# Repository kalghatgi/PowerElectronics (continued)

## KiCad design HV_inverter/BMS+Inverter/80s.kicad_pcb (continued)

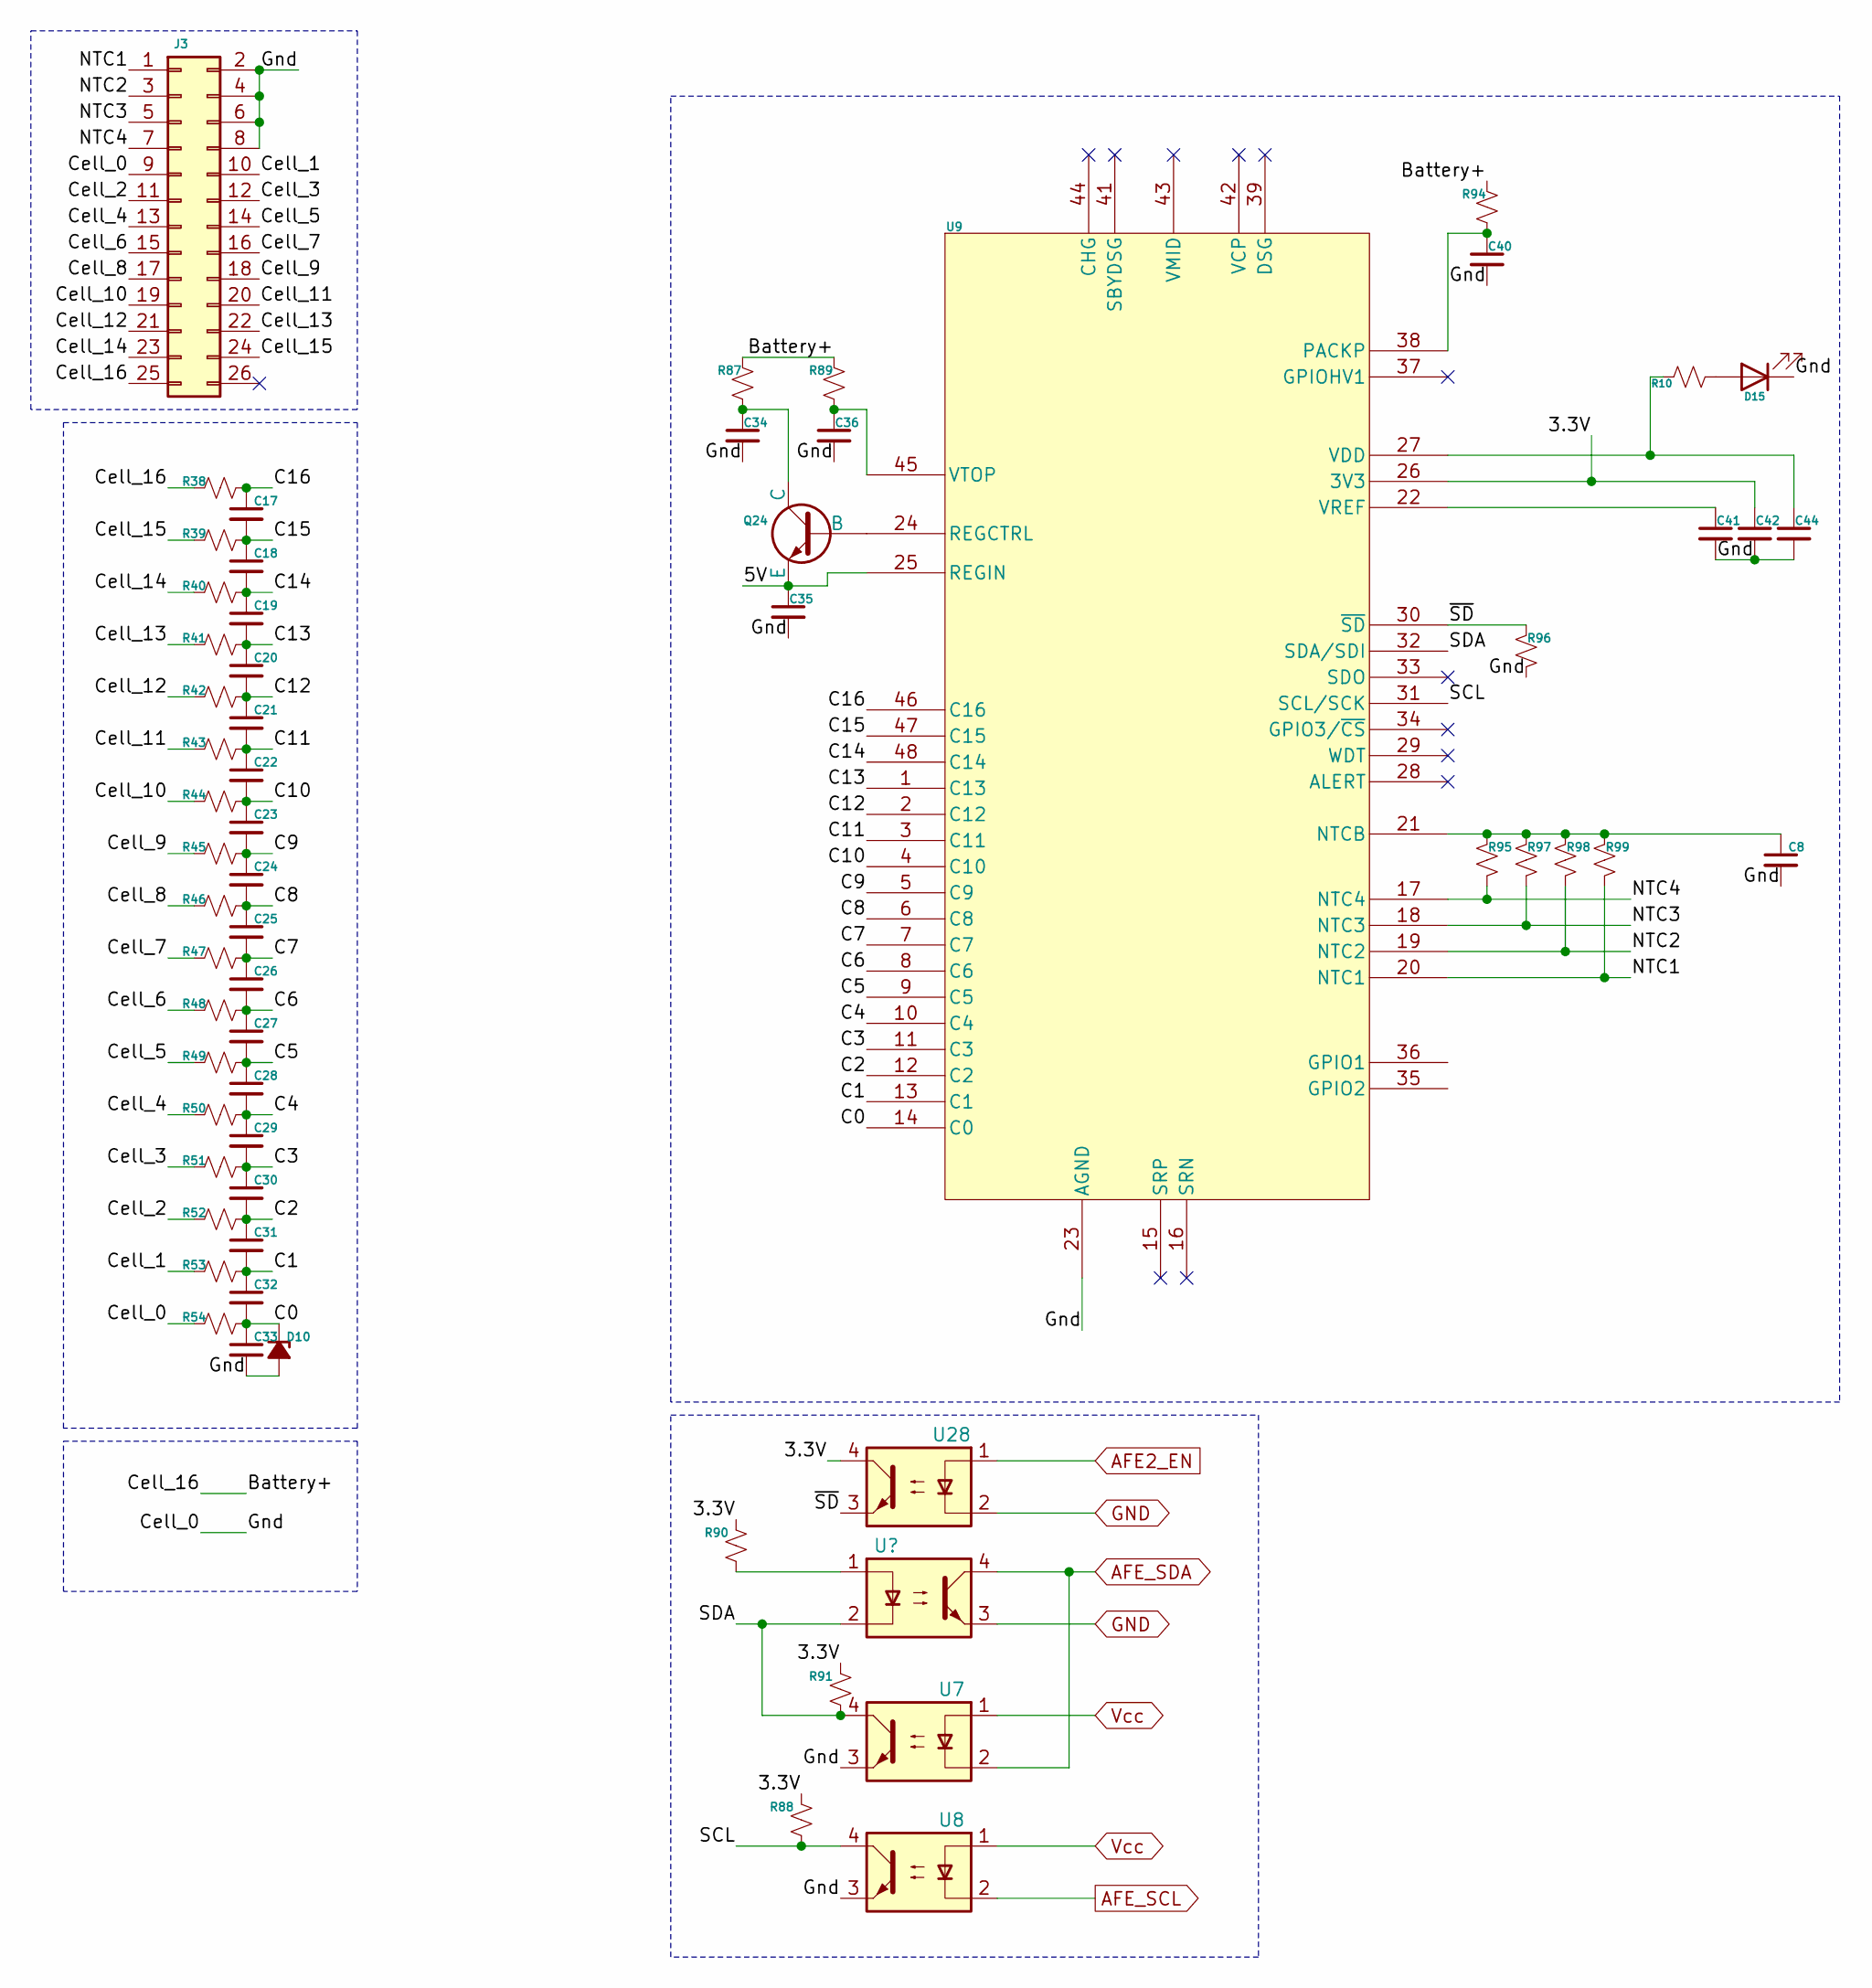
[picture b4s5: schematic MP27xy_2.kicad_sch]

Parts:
C8, C17, C18, C19, C20, C21, C22, C23, C24, C25, C26, C27, C28, C29, C30, C31, C32, C33: 10000pF, >=10V, 0402; C_0402_1005Metric; MPN grm155r61c103ka01d
C34: 1uF, >=100V, 0805; C_0805_2012Metric; MPN grm21bc72a105ke01l
C35: 3.3uF, >=10V, 0402; C_0402_1005Metric
C36: 0.47uF, >=100V, 0805; C_0805_2012Metric; MPN cc0805kkx7r0bb474
C40: 10nF, >=100V, 0805; C_0805_2012Metric; MPN c0805c103k1ractu
C41, C42, C44: 1uF, >=6.3V, 0402; C_0402_1005Metric; MPN cl05a105kq5nnnc
D10: VR=3.3V; D_SOD-323; MPN bzx384c3v3-e3-08
D15: LED-Red 0402; LED_0402_1005Metric
J3: 2x13 pin; IDC-Header_2x13_P2.54mm_Horizontal
Q24: NPN, 80V, 0.5A; SOT-23; MPN mmbt5550lt1g
R10, R95, R96, R97, R98, R99: 10K, >=62.5mW, 0402; R_0402_1005Metric; MPN mcwr04x1002ftl
R38, R39, R40, R41, R42, R43, R44, R45, R46, R47, R48, R49, R50, R51, R52, R53, R54: 1K, >=62.5mW, 0402; R_0402_1005Metric; MPN mcwr04x1001ftl
R87: 500E, >=100mW, 0603; R_0603_1608Metric; MPN rt0603brc07500rl
R88, R90, R91: 1.5K, >=62.5mW, 0402; R_0402_1005Metric; MPN mcwr04x1501ftl
R89: 20E, >=100mW, 0603; R_0603_1608Metric; MPN mcwr06x20r0ftl
R94: 100E, >=100mW, 0603; R_0603_1608Metric; MPN mcwr06x101-jtl
U6, U7, U8, U28: PC817; DIP-4_W7.62mm
U9: MP2787; TQFP-48_7x7mm_P0.5mm; MPN MP2787DFP-0001-T

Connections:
/CMU2/3.3V: C42.1, R88.2, R90.2, R91.2, U9.26 (3V3), U28.4
/CMU2/5V: C35.1, Q24.2 (E), U9.25 (REGIN)
/CMU2/Battery+: J3.25, R38.2, R87.2, R89.2, R94.2
/CMU2/C0: C32.2, C33.1, D10.1 (K), R54.1, U9.14 (C0)
/CMU2/C1: C31.2, C32.1, R53.1, U9.13 (C1)
/CMU2/C2: C30.2, C31.1, R52.1, U9.12 (C2)
/CMU2/C3: C29.2, C30.1, R51.1, U9.11 (C3)
/CMU2/C4: C28.2, C29.1, R50.1, U9.10 (C4)
/CMU2/C5: C27.2, C28.1, R49.1, U9.9 (C5)
/CMU2/C6: C26.2, C27.1, R48.1, U9.8 (C6)
/CMU2/C7: C25.2, C26.1, R47.1, U9.7 (C7)
/CMU2/C8: C24.2, C25.1, R46.1, U9.6 (C8)
/CMU2/C9: C23.2, C24.1, R45.1, U9.5 (C9)
/CMU2/C10: C22.2, C23.1, R44.1, U9.4 (C10)
/CMU2/C11: C21.2, C22.1, R43.1, U9.3 (C11)
/CMU2/C12: C20.2, C21.1, R42.1, U9.2 (C12)
/CMU2/C13: C19.2, C20.1, R41.1, U9.1 (C13)
/CMU2/C14: C18.2, C19.1, R40.1, U9.48 (C14)
/CMU2/C15: C17.2, C18.1, R39.1, U9.47 (C15)
/CMU2/C16: C17.1, R38.1, U9.46 (C16)
/CMU2/Cell_0: C8.2, C33.2, C34.2, C35.2, C36.2, C40.2, C41.2, C42.2, C44.2, D10.2 (A), D15.1 (K), J3.2, J3.4, J3.6, J3.8, J3.9, R54.2, R96.2, U7.3, U8.3, U9.23 (AGND)
/CMU2/Cell_1: J3.10, R53.2
/CMU2/Cell_2: J3.11, R52.2
/CMU2/Cell_3: J3.12, R51.2
/CMU2/Cell_4: J3.13, R50.2
/CMU2/Cell_5: J3.14, R49.2
/CMU2/Cell_6: J3.15, R48.2
/CMU2/Cell_7: J3.16, R47.2
/CMU2/Cell_8: J3.17, R46.2
/CMU2/Cell_9: J3.18, R45.2
/CMU2/Cell_10: J3.19, R44.2
/CMU2/Cell_11: J3.20, R43.2
/CMU2/Cell_12: J3.21, R42.2
/CMU2/Cell_13: J3.22, R41.2
/CMU2/Cell_14: J3.23, R40.2
/CMU2/Cell_15: J3.24, R39.2
/CMU2/NTC1: J3.1, R99.2, U9.20 (NTC1)
/CMU2/NTC2: J3.3, R98.2, U9.19 (NTC2)
/CMU2/NTC3: J3.5, R97.2, U9.18 (NTC3)
/CMU2/NTC4: J3.7, R95.2, U9.17 (NTC4)
/CMU2/SCL: R88.1, U8.4, U9.31 (SCL/SCK)
/CMU2/SDA: R91.1, U6.2, U7.4, U9.32 (SDA/SDI)
/CMU2/~SD: R96.1, U9.30 (~SD), U28.3
AFE2_EN: U28.1; also elsewhere on the board
AFE_SCL: U8.2; also elsewhere on the board
AFE_SDA: U6.4, U7.2; also elsewhere on the board
GND: U6.3, U28.2; also elsewhere on the board
unnamed: D15.2 (A), R10.1
unnamed: Q24.1 (B), U9.24 (REGCTRL)
unnamed: C34.1, Q24.3 (C), R87.1
unnamed: R90.1, U6.1
unnamed: C8.1, R95.1, R97.1, R98.1, R99.1, U9.21 (NTCB)
unnamed: C40.1, R94.1, U9.38 (PACKP)
unnamed: C44.1, R10.2, U9.27 (VDD)
unnamed: C41.1, U9.22 (VREF)
unnamed: C36.1, R89.1, U9.45 (VTOP)
Vcc: U7.1, U8.1; also elsewhere on the board

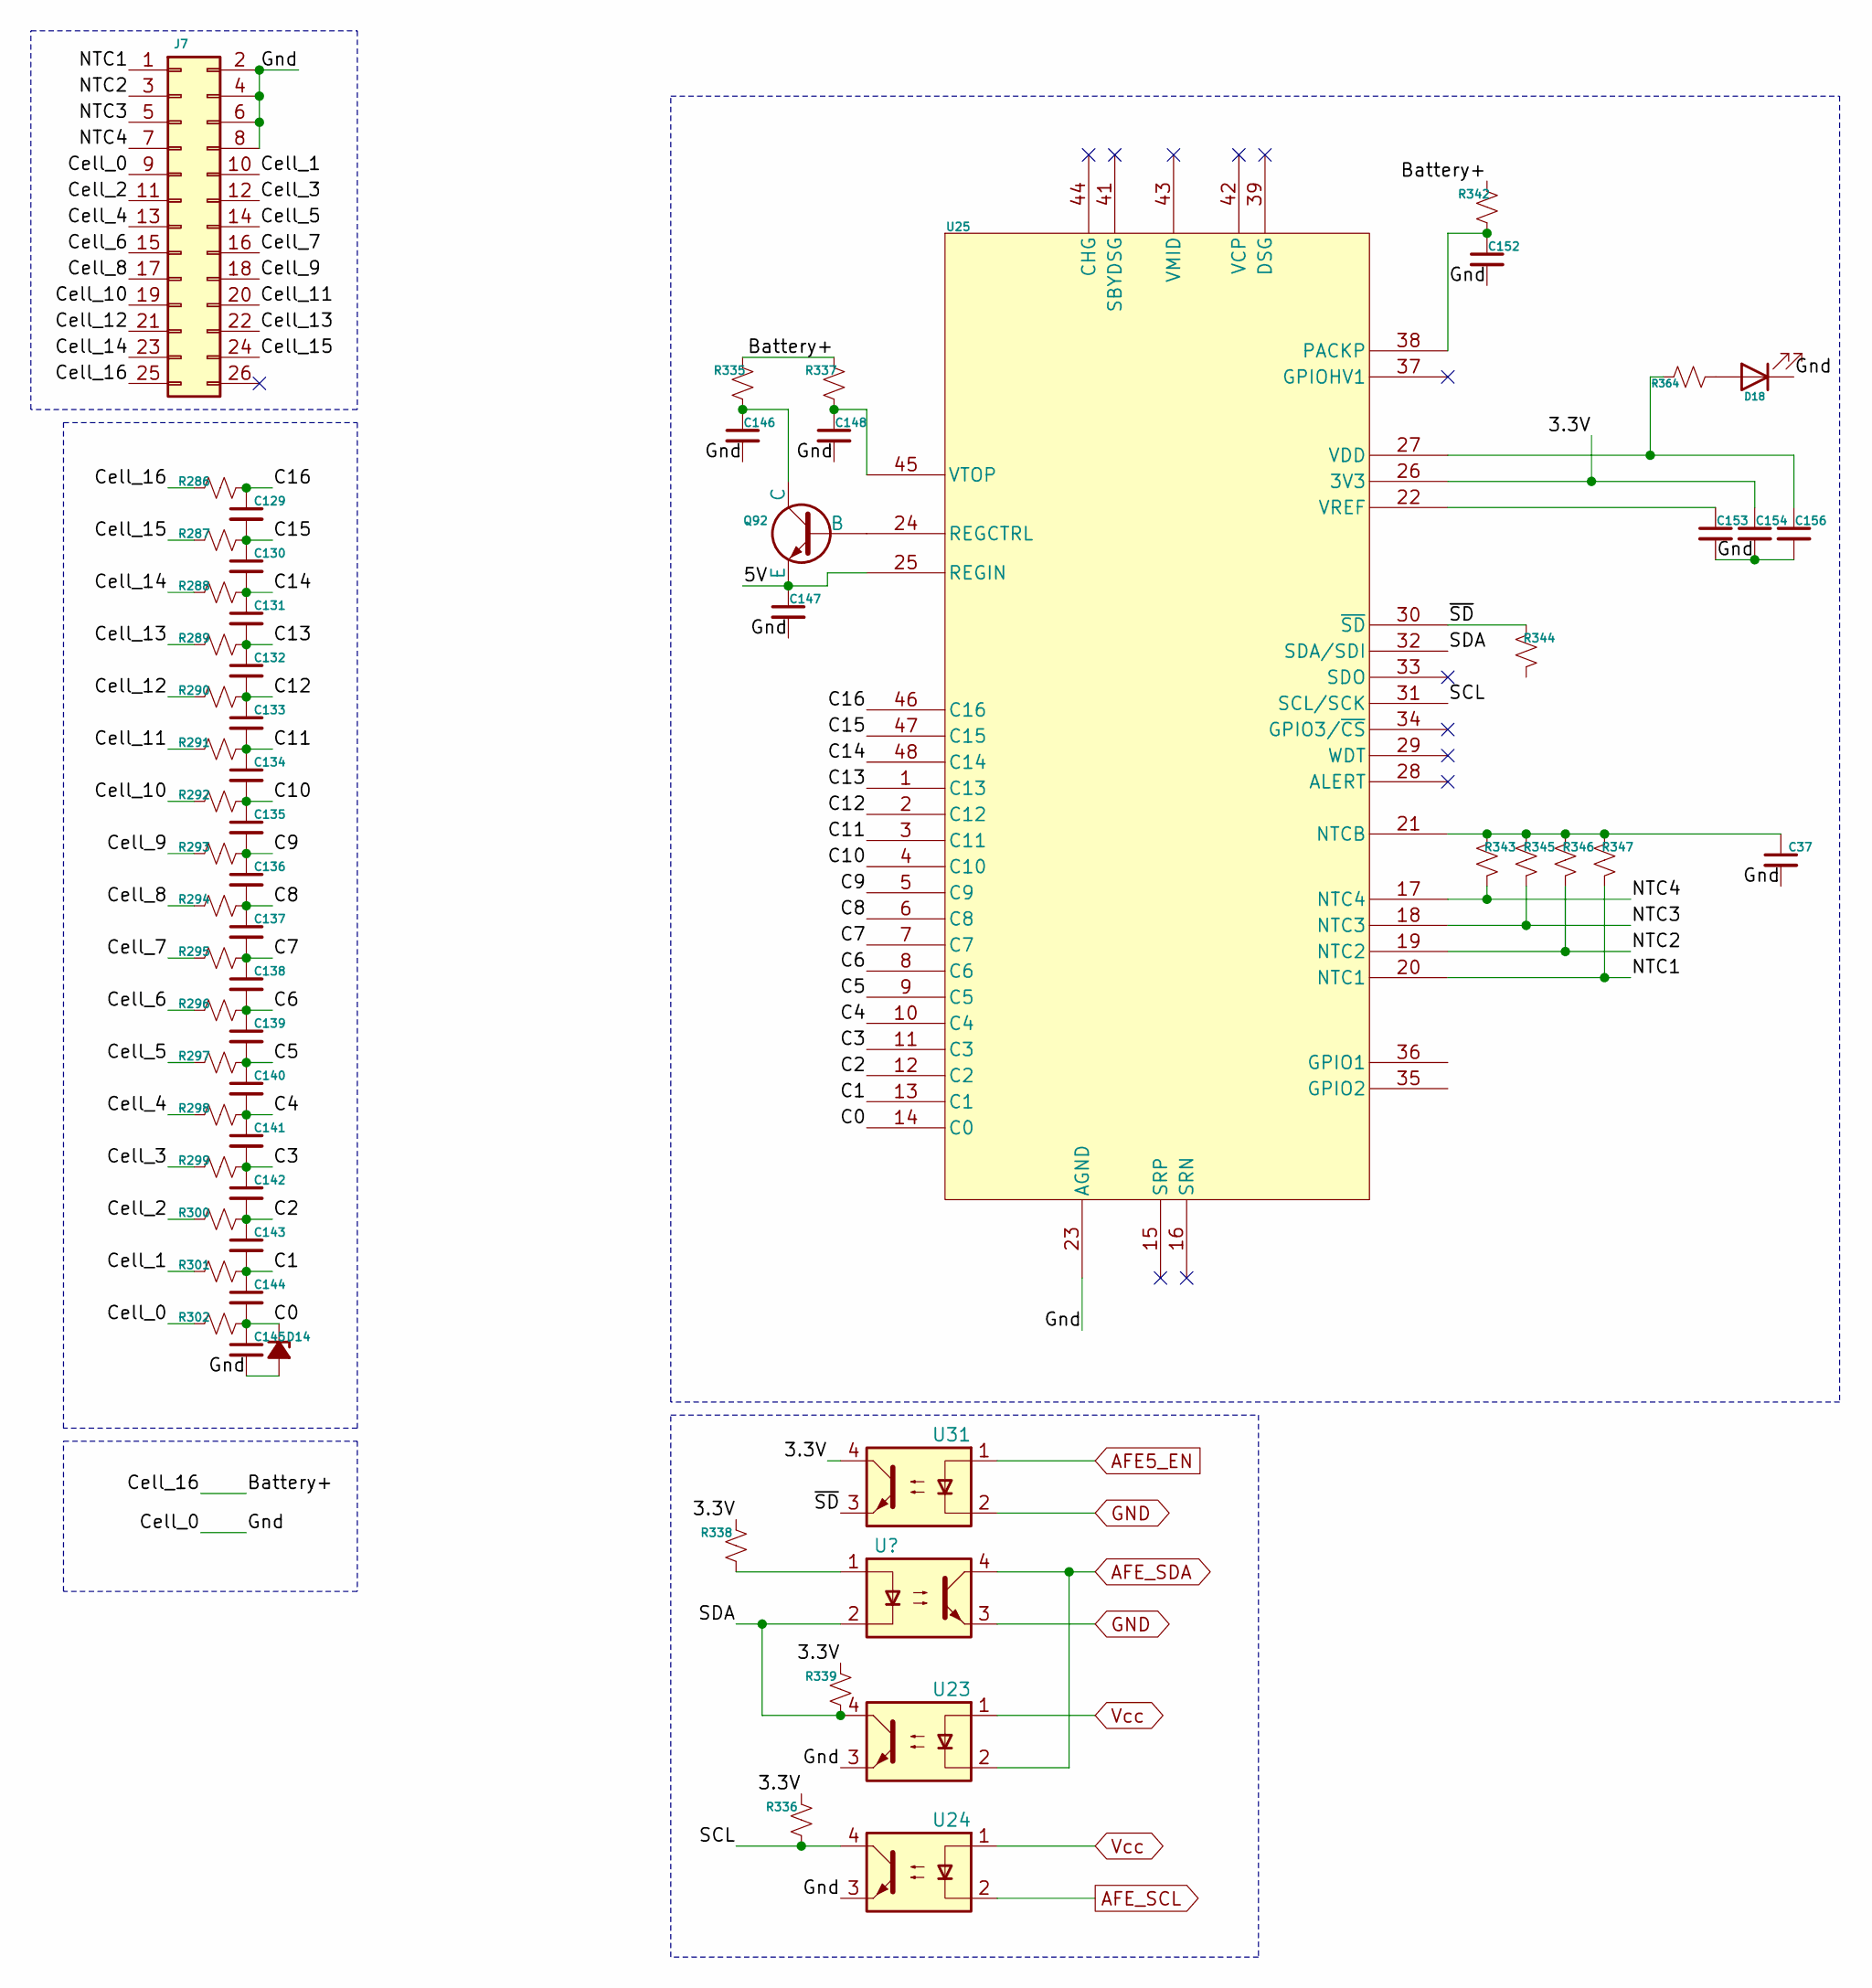
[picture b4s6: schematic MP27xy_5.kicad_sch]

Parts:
C37, C129, C130, C131, C132, C133, C134, C135, C136, C137, C138, C139, C140, C141, C142, C143, C144, C145: 10000pF, >=10V, 0402; C_0402_1005Metric; MPN grm155r61c103ka01d
C146: 1uF, >=100V, 0805; C_0805_2012Metric; MPN grm21bc72a105ke01l
C147: 3.3uF, >=10V, 0402; C_0402_1005Metric
C148: 0.47uF, >=100V, 0805; C_0805_2012Metric; MPN cc0805kkx7r0bb474
C152: 10nF, >=100V, 0805; C_0805_2012Metric; MPN c0805c103k1ractu
C153, C154, C156: 1uF, >=6.3V, 0402; C_0402_1005Metric; MPN cl05a105kq5nnnc
D14: VR=3.3V; D_SOD-323; MPN bzx384c3v3-e3-08
D18: LED-Red 0402; LED_0402_1005Metric
J7: 2x13 pin; IDC-Header_2x13_P2.54mm_Horizontal
Q92: NPN, 80V, 0.5A; SOT-23; MPN mmbt5550lt1g
R286, R287, R288, R289, R290, R291, R292, R293, R294, R295, R296, R297, R298, R299, R300, R301, R302: 1K, >=62.5mW, 0402; R_0402_1005Metric; MPN mcwr04x1001ftl
R335: 500E, >=100mW, 0603; R_0603_1608Metric; MPN rt0603brc07500rl
R336, R338, R339: 1.5K, >=62.5mW, 0402; R_0402_1005Metric; MPN mcwr04x1501ftl
R337: 20E, >=100mW, 0603; R_0603_1608Metric; MPN mcwr06x20r0ftl
R342: 100E, >=100mW, 0603; R_0603_1608Metric; MPN mcwr06x101-jtl
R343, R344, R345, R346, R347, R364: 10K, >=62.5mW, 0402; R_0402_1005Metric; MPN mcwr04x1002ftl
U22, U23, U24, U31: PC817; DIP-4_W7.62mm
U25: MP2787; TQFP-48_7x7mm_P0.5mm; MPN MP2787DFP-0001-T

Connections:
/CMU5/3.3V: C154.1, R336.2, R338.2, R339.2, U25.26 (3V3), U31.4
/CMU5/5V: C147.1, Q92.2 (E), U25.25 (REGIN)
/CMU5/Battery+: J7.25, R286.2, R335.2, R337.2, R342.2
/CMU5/C0: C144.2, C145.1, D14.1 (K), R302.1, U25.14 (C0)
/CMU5/C1: C143.2, C144.1, R301.1, U25.13 (C1)
/CMU5/C2: C142.2, C143.1, R300.1, U25.12 (C2)
/CMU5/C3: C141.2, C142.1, R299.1, U25.11 (C3)
/CMU5/C4: C140.2, C141.1, R298.1, U25.10 (C4)
/CMU5/C5: C139.2, C140.1, R297.1, U25.9 (C5)
/CMU5/C6: C138.2, C139.1, R296.1, U25.8 (C6)
/CMU5/C7: C137.2, C138.1, R295.1, U25.7 (C7)
/CMU5/C8: C136.2, C137.1, R294.1, U25.6 (C8)
/CMU5/C9: C135.2, C136.1, R293.1, U25.5 (C9)
/CMU5/C10: C134.2, C135.1, R292.1, U25.4 (C10)
/CMU5/C11: C133.2, C134.1, R291.1, U25.3 (C11)
/CMU5/C12: C132.2, C133.1, R290.1, U25.2 (C12)
/CMU5/C13: C131.2, C132.1, R289.1, U25.1 (C13)
/CMU5/C14: C130.2, C131.1, R288.1, U25.48 (C14)
/CMU5/C15: C129.2, C130.1, R287.1, U25.47 (C15)
/CMU5/C16: C129.1, R286.1, U25.46 (C16)
/CMU5/Cell_0: C37.2, C145.2, C146.2, C147.2, C148.2, C152.2, C153.2, C154.2, C156.2, D14.2 (A), D18.1 (K), J7.2, J7.4, J7.6, J7.8, J7.9, R302.2, U23.3, U24.3, U25.23 (AGND)
/CMU5/Cell_1: J7.10, R301.2
/CMU5/Cell_2: J7.11, R300.2
/CMU5/Cell_3: J7.12, R299.2
/CMU5/Cell_4: J7.13, R298.2
/CMU5/Cell_5: J7.14, R297.2
/CMU5/Cell_6: J7.15, R296.2
/CMU5/Cell_7: J7.16, R295.2
/CMU5/Cell_8: J7.17, R294.2
/CMU5/Cell_9: J7.18, R293.2
/CMU5/Cell_10: J7.19, R292.2
/CMU5/Cell_11: J7.20, R291.2
/CMU5/Cell_12: J7.21, R290.2
/CMU5/Cell_13: J7.22, R289.2
/CMU5/Cell_14: J7.23, R288.2
/CMU5/Cell_15: J7.24, R287.2
/CMU5/NTC1: J7.1, R347.2, U25.20 (NTC1)
/CMU5/NTC2: J7.3, R346.2, U25.19 (NTC2)
/CMU5/NTC3: J7.5, R345.2, U25.18 (NTC3)
/CMU5/NTC4: J7.7, R343.2, U25.17 (NTC4)
/CMU5/SCL: R336.1, U24.4, U25.31 (SCL/SCK)
/CMU5/SDA: R339.1, U22.2, U23.4, U25.32 (SDA/SDI)
/CMU5/~SD: R344.1, U25.30 (~SD), U31.3
AFE5_EN: U31.1; also elsewhere on the board
AFE_SCL: U24.2; also elsewhere on the board
AFE_SDA: U22.4, U23.2; also elsewhere on the board
GND: U22.3, U31.2; also elsewhere on the board
unnamed: D18.2 (A), R364.1
unnamed: Q92.1 (B), U25.24 (REGCTRL)
unnamed: C146.1, Q92.3 (C), R335.1
unnamed: R338.1, U22.1
unnamed: C37.1, R343.1, R345.1, R346.1, R347.1, U25.21 (NTCB)
unnamed: C152.1, R342.1, U25.38 (PACKP)
unnamed: C156.1, R364.2, U25.27 (VDD)
unnamed: C153.1, U25.22 (VREF)
unnamed: C148.1, R337.1, U25.45 (VTOP)
Vcc: U23.1, U24.1; also elsewhere on the board

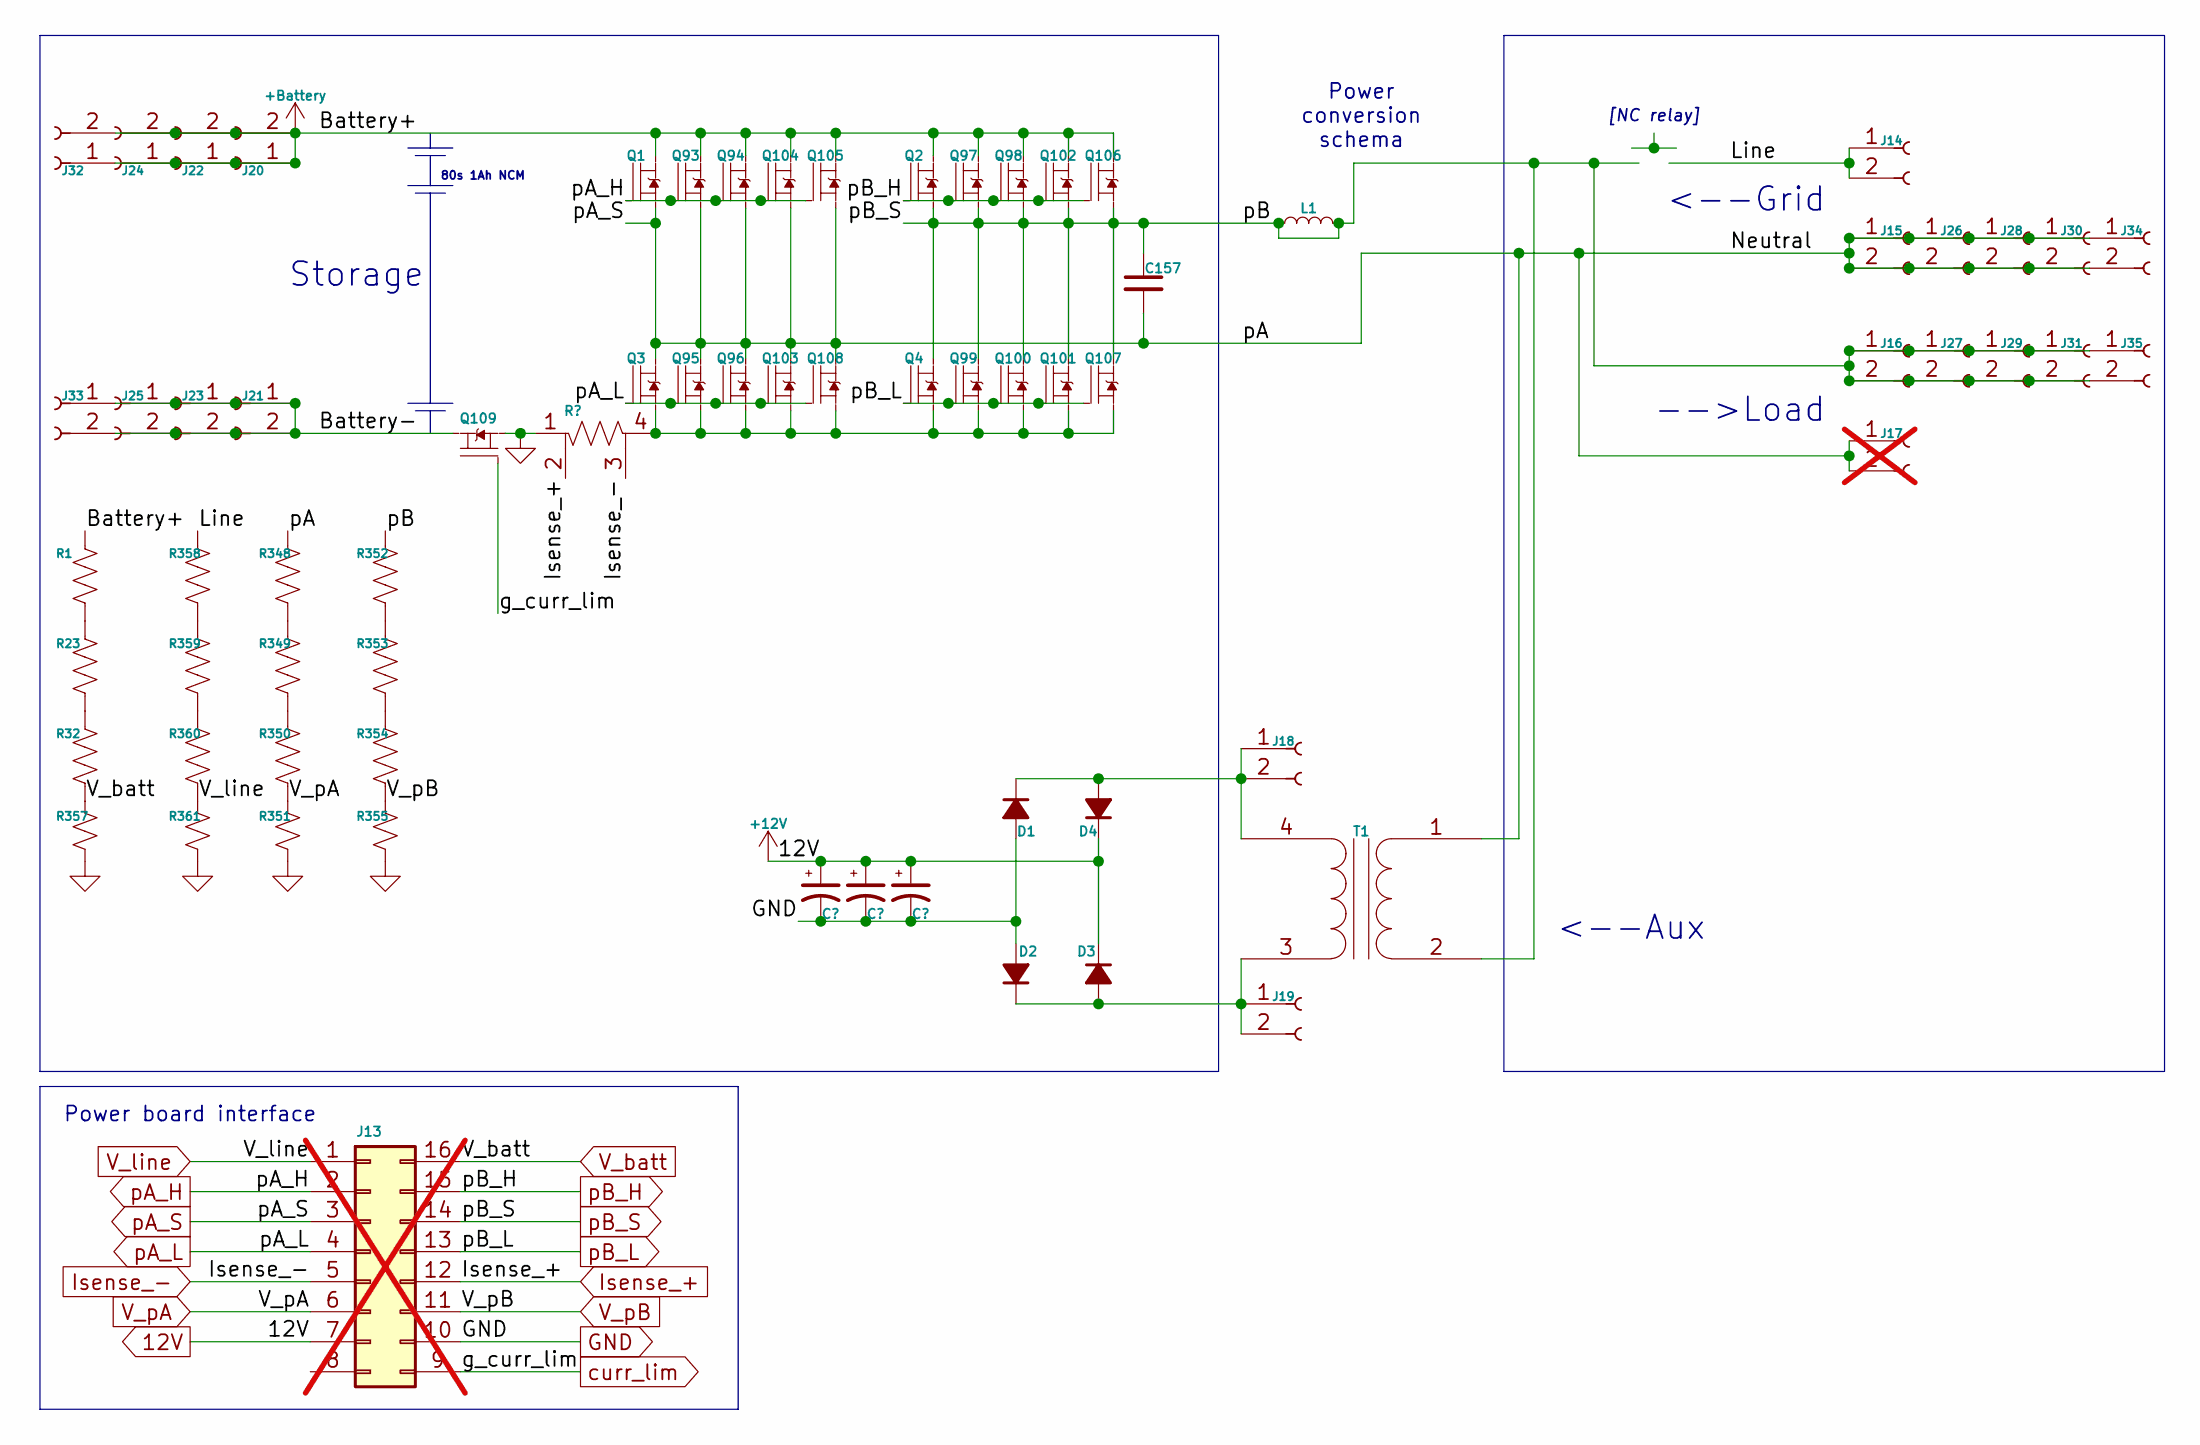
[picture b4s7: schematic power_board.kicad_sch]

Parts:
C157: 1uF, >500V; C_2220_5750Metric; MPN 2220CC105KAZ2A
C159, C160, C161: 100uF, >25V; C_Radial_D6.3mm_H5.0mm_P2.50mm
D1, D2, D3, D4: Vr>400V, If>2A; D_SOD-123F; MPN SL1A
J13: 2x7 pin, 2.54mm pitch; PinSocket_2x07_P2.54mm_Vertical; not fitted
J14, J15, J16, J18, J19, J20, J21, J22, J23, J24, J25, J26, J27, J28, J29, J30, J31, J32, J33, J34, J35: 2pin, >400V, >20A; TE_62409-1; MPN DJ6112
J17: 2pin, >400V, >20A; TE_62409-1; MPN DJ6112; not fitted
L1: L_Small
Q1, Q2, Q3, Q4, Q93, Q94, Q95, Q96, Q97, Q98, Q99, Q100, Q101, Q102, Q103, Q104, Q105, Q106, Q107, Q108: NMOS, Vds>=400V, Rds<=50mOhm; IPDQ60R037CM8XTMA1; MPN IPDQ60R037CM8XTMA1
Q109: NMOS, Vds>=80V, Rds<=2mOhm; Infineon_PG-TDSON-8_6.15x5.15mm; MPN IAUCN08S7N013ATMA1
R1, R23, R32, R348, R349, R350, R352, R353, R354, R358, R359, R360: 1MOhm, >200V, <1%, >62.5mW; R_1206_3216Metric
R351, R355, R357, R361: 10K, >62.5mW; R_0603_1608Metric
R356: 10mOhm, >=3W; R_shunt_2512_6332Metric; MPN CRA2512-FZ-R010ELF
T1: Vin=230V, Vout=12V, Iout=0.3A

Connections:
12V: C159.1, C160.1, C161.1, D3.1 (K), D4.1 (K), J13.7; also elsewhere on the board
+Battery: J20.1, J20.2, J22.1, J22.2, J24.1, J24.2, J32.1, J32.2, Q1.3 (D), Q2.3 (D), Q93.3 (D), Q94.3 (D), Q97.3 (D), Q98.3 (D), Q102.3 (D), Q104.3 (D), Q105.3 (D), Q106.3 (D), R1.1
/Power/Battery-: J21.1, J21.2, J23.1, J23.2, J25.1, J25.2, J33.1, J33.2, Q109.5 (D)
/Power/Line: J14.1, J14.2, R358.1
GND: C159.2, C160.2, C161.2, D1.2 (A), D2.2 (A), J13.10, Q109.1 (S), Q109.2 (S), Q109.3 (S), R351.2, R355.2, R356.1, R357.2, R361.2; also elsewhere on the board
Isense_+: J13.12, R356.2; also elsewhere on the board
Isense_-: J13.5, R356.3; also elsewhere on the board
unnamed: D1.1 (K), D4.2 (A), J18.1, J18.2, T1.4 (SB)
unnamed: D2.1 (K), D3.2 (A), J19.1, J19.2, T1.3 (SA)
unnamed: Q3.2 (S), Q4.2 (S), Q95.2 (S), Q96.2 (S), Q99.2 (S), Q100.2 (S), Q101.2 (S), Q103.2 (S), Q107.2 (S), Q108.2 (S), R356.4
unnamed: R1.2, R23.1
unnamed: R23.2, R32.1
unnamed: R348.2, R349.1
unnamed: R349.2, R350.1
unnamed: R352.2, R353.1
unnamed: R353.2, R354.1
unnamed: R358.2, R359.1
unnamed: R359.2, R360.1
V_batt: J13.16, R32.2, R357.1; also elsewhere on the board
V_line: J13.1, R360.2, R361.1; also elsewhere on the board
V_pA: J13.6, R350.2, R351.1; also elsewhere on the board
V_pB: J13.11, R354.2, R355.1; also elsewhere on the board
curr_lim: J13.9, Q109.4 (G); also elsewhere on the board
pA_H: J13.2, Q1.1 (G), Q93.1 (G), Q94.1 (G), Q104.1 (G), Q105.1 (G); also elsewhere on the board
pA_L: J13.4, Q3.1 (G), Q95.1 (G), Q96.1 (G), Q103.1 (G), Q108.1 (G); also elsewhere on the board
pA_S: C157.2, J13.3, J15.1, J15.2, J17.1, J17.2, J26.1, J26.2, J28.1, J28.2, J30.1, J30.2, J34.1, J34.2, Q1.2 (S), Q3.3 (D), Q93.2 (S), Q94.2 (S), Q95.3 (D), Q96.3 (D), Q103.3 (D), Q104.2 (S), Q105.2 (S), Q108.3 (D), R348.1, T1.1 (AA); also elsewhere on the board
pB_H: J13.15, Q2.1 (G), Q97.1 (G), Q98.1 (G), Q102.1 (G), Q106.1 (G); also elsewhere on the board
pB_L: J13.13, Q4.1 (G), Q99.1 (G), Q100.1 (G), Q101.1 (G), Q107.1 (G); also elsewhere on the board
pB_S: C157.1, J13.14, J16.1, J16.2, J27.1, J27.2, J29.1, J29.2, J31.1, J31.2, J35.1, J35.2, L1.1, L1.2, Q2.2 (S), Q4.3 (D), Q97.2 (S), Q98.2 (S), Q99.3 (D), Q100.3 (D), Q101.3 (D), Q102.2 (S), Q106.2 (S), Q107.3 (D), R352.1, T1.2 (AB); also elsewhere on the board

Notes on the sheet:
80s 1Ah NCM
Storage
<--Aux
-->Load
Power board interface
<--Grid
Power conversion schema
[NC relay]

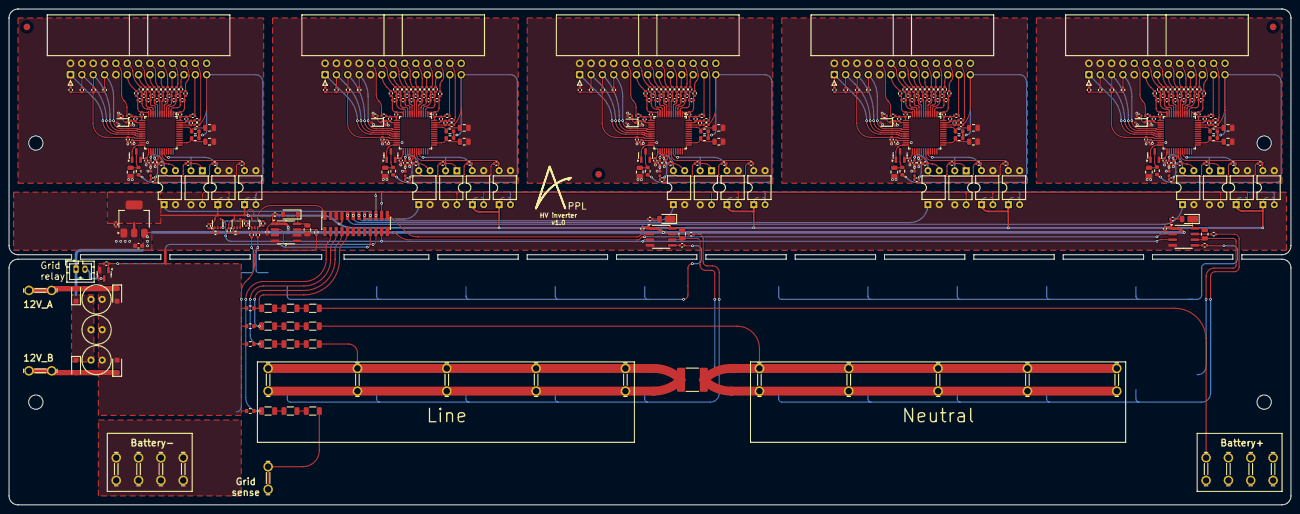
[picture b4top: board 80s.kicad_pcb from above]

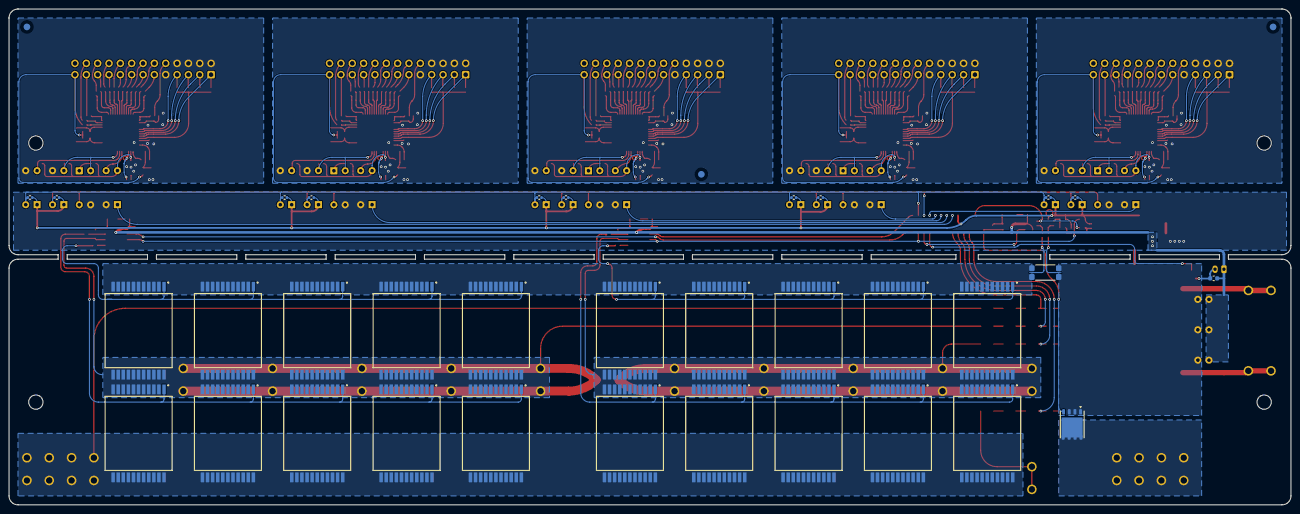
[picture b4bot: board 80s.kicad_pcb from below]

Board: 2 copper layers, 287.0 x 111.0 mm, 441 parts (36 on the bottom side), 320 nets.
